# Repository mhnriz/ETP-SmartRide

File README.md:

# ETP-SmartRide: Smart Transit & Monitoring System
**Status:** Functional Prototype Handed Over
**Date:** January 2026

## 📌 Project Overview
ETP-SmartRide is an IoT-based transit system designed to improve bus efficiency and passenger experience. The system integrates real-time seat occupancy tracking, GPS location monitoring, and a Smart Bus Stop ETA display. 

The project was executed in two phases:
1. **Phase 1 (Planning):** Research, Power Budgeting, and Circuit Drafting.
2. **Phase 2 (Execution):** Hardware integration, ESP-NOW communication, and Firebase Cloud syncing.

## ⚙️ System Architecture
Due to hardware logistics, the current prototype uses a **Modular ESP32 Mesh** rather than a Raspberry Pi master.

* **Master Node (ESP32):** Acts as the Cloud Gateway. It fetches booking data from Firebase via WiFi and broadcasts seat status to nodes.
* **Slave Nodes (ESP32):** Distributed across the bus. Each node manages 4 seats, controlling bi-color LEDs and ultrasonic sensors.
* **Communication:** Internal data is sent via **ESP-NOW** for low-latency, while external data uses **HTTPS/Firebase**.
* **Bus Stop Display:** Uses the same Master circuit to fetch ETA data and output to a 22" monitor.

## 🔋 Hardware & Power Specifications
The system is designed for mobility and sustainability:
- **Power Source:** 100W Monocrystalline Solar Panel [B-18].
- **Storage:** 15AH 12V AGM Solar Battery [B-20].
- **Regulation:** LM2596 Buck-down modules regulated to 5V for logic circuits.
- **Enclosures:** Custom 3D-printed PLA housings.

> **⚠️ HANDOVER NOTE:** All LM2596 buck converters must be verified with a multimeter for stable 5V output before connecting the ESP32 or Pi.

## 📂 Repository Structure
- `/firmware`: Contains `.ino` files for the Bus Master, Bus Stop, and Seat Nodes.
- `/hardware`: Contains the archived KiCad project files (`.zip`) and PDF schematics.
- `/hardware/parts_list.md`: Full Bill of Materials (BOM) with IDs.
- `/docs`: Power budgeting, initial planning documents, and architecture diagrams.
- `HANDOVER.md`: Technical guide for the incoming 8-month team.

## 🚀 Quick Start (Prototype Mode)
1. **Configure WiFi:** Update `ssid` and `password` in the `master_esp32.ino`.
2. **Firebase:** Ensure your `FIREBASE_TOKEN` and URL match your Firestore instance.
3. **Flash Nodes:** Flash the `slave_node.ino` to the respective ESP32s using the MAC addresses listed in the Master code.

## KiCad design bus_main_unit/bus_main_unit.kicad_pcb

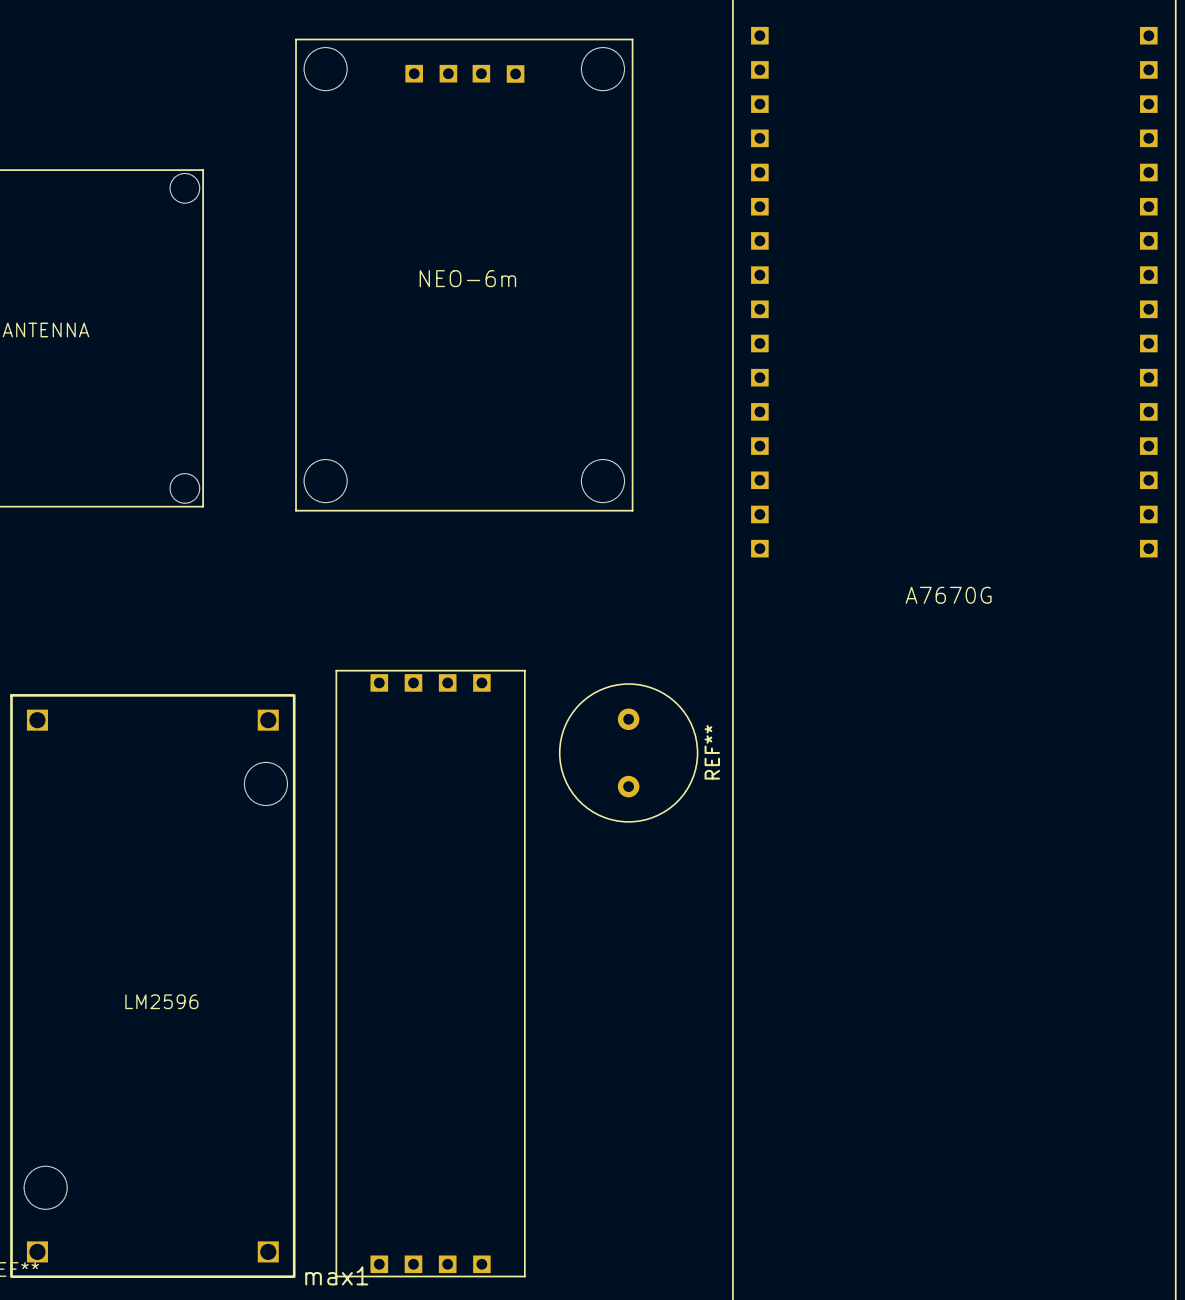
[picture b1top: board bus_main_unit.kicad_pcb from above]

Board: 2 copper layers, 4 parts (0 on the bottom side), 5 nets, no tracks yet.

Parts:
A1: A7670G
antenna1: ANTENNA
max1: max485
neo-6m1: NEO-6m_breakout_board

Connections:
unnamed: A1.33, max1.DI
unnamed: A1.RXD, neo-6m1.TX
unnamed: A1.TXD, neo-6m1.RX
unnamed: A1.VBAT, max1.DE, max1.RE, max1.VCC, neo-6m1.VCC
unnamed: max1.GND, neo-6m1.GND

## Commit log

2025-07-06 Create sketch.ino for ESP32
    Setup WiFi + supabase, fetch and parse json for interaction with ATtiny2313, early stage
2025-07-06 feat: optimize Supabase fetch with connection reuse and ATtiny LED mapping
    - Added UART setup for ATtiny2313 integration (Serial2 TX pin 17)
    - Implemented connection reuse using http.setReuse(true) to reduce fetch time
    - Parsed Supabase JSON and mapped seat status to 11 ATtiny string arrays
    - Prepared LED status string (4 bits each) to later send over UART
    - Added payload size and timing debug logs
    - Updated loop with 10-second polling interval for lower power consumption
2025-09-23 move bus_unit/sketch.ino to bus-node/sketch/sketch.ino
2025-09-23 move bus_main_unit/bus_main_unit.kicad_pcb to hardware/bus_main_unit/bus_main_unit.kicad_pcb
2025-09-23 move layout.png to layout.png
2025-09-23 move hardbus_main_unit/layout.png to hardware/bus_main_unit/layout.png
2025-09-23 move bus_seat_unit/bus_seat_unit.kicad_pcb to hardware/bus_seat_unit/bus_seat_unit.kicad_pcb
2025-09-23 move bus_seat_unit/layout.png to hardware/bus_seat_unit/layout.png
2025-09-23 move bus_power_unit/bus_power_unit.kicad_pcb to hardware/bus_power_unit/bus_power_unit.kicad_pcb
2025-09-23 move bus_power_unit/layout.png to hardware/bus_power_unit/layout.png
2026-01-12 Final Handover: Archived legacy files and added full Phase 2 documentation
